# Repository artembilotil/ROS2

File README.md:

# Самостійна робота 1. ROS 2: workspace, ООП-nodes та ESP32 через micro-ROS

**Студент:** Artem Bilotil
**Група:** Рт-2

**Workspace:** `ros2_stud_bilotil_ws`
**Пакет C++:** `stud_bilotil_cpp_pkg`
**Пакет Python:** `stud_bilotil_py_pkg`
**Основний topic (текстові повідомлення):** `/stud_bilotil/message`

---

## Схема системи (поточний стан, Етапи 1–7)

```text
                 ros2_stud_bilotil_ws
                          │
         ┌────────────────┴────────────────┐
         │                                  │
  stud_bilotil_cpp_pkg              stud_bilotil_py_pkg
         │                                  │
 stud_bilotil_publisher      stud_bilotil_subscriber_1/2/3
         │                                  │
         └────────► /stud_bilotil/message ◄─┘
```

---

## 1. Правило іменування

| Об'єкт                        | Ім'я                                   |
|-------------------------------|----------------------------------------|
| Workspace                     | `ros2_stud_bilotil_ws`                 |
| C++ package                   | `stud_bilotil_cpp_pkg`                 |
| Python package                | `stud_bilotil_py_pkg`                  |
| Node — publisher              | `stud_bilotil_publisher`               |
| Node — subscriber             | `stud_bilotil_subscriber`              |
| Node — монітор температури    | `stud_bilotil_temperature_monitor`     |
| Node на мікроконтролері       | `stud_bilotil_esp32`                   |
| Topic — текстові повідомлення | `/stud_bilotil/message`                |
| Topic — температура, °C       | `/stud_bilotil/temperature/celsius`    |
| Topic — температура, °F       | `/stud_bilotil/temperature/fahrenheit` |

---

## 2. Стиль коду

Обидва nodes реалізовано класами:

- `StudentPublisher` успадковує `rclcpp::Node` (C++), усі ROS-сутності (`publisher_`,
  `timer_`, `counter_`) — приватні поля класу, `main()` містить лише
  `rclcpp::init()` → `std::make_shared<StudentPublisher>()` → `rclcpp::spin()` →
  `rclcpp::shutdown()`.
- `StudentSubscriber` успадковує `rclpy.node.Node` (Python), конструктор викликає
  `super().__init__(...)`, `listener_callback` — метод класу.

---

## 3. Етап 1. Власний workspace

### Структура каталогів

| Каталог | Опис |
|---|---|
| `src` | Містить початковий вихідний код (source code) усіх створених або завантажених пакетів ROS 2. |
| `build` | Використовується системою збірки `colcon` для зберігання проміжних файлів компіляції та конфігурації. |
| `install` | Містить готові зібрані виконувані файли, бібліотеки, скрипти та `setup.bash` для їх підключення до середовища. |
| `log` | Зберігає текстові файли журналів (логів) із детальним звітом про процес виконання команд `colcon build`. |

### Вивід перевірки

```text
ros@ros:~/ros2_stud_bilotil_ws$ printenv | grep ROS
ROS_VERSION=2
ROS_PYTHON_VERSION=3
ROS_AUTOMATIC_DISCOVERY_RANGE=SUBNET
ROS_DISTRO=jazzy

ros@ros:~/ros2_stud_bilotil_ws$echo$AMENT_PREFIX_PATH
/home/ros/ros2_stud_bilotil_ws/install/stud_bilotil_py_pkg:/home/ros/ros2_stud_bilotil_ws/install/stud_bilotil_cpp_pkg:/opt/ros/jazzy

### Чому `install/setup.bash` підключається після `/opt/ros/jazzy/setup.bash`, а не замість нього

Файл `install/setup.bash` локального workspace підключається після системного
`/opt/ros/jazzy/setup.bash`, оскільки ROS 2 працює за принципом каскадного накладання
середовищ (underlay / overlay). Системний ROS 2 надає базовий фреймворк, стандартні
бібліотеки та типи повідомлень, а локальний workspace будується поверх нього і
додає власні пакети. Послідовне підключення дописує шляхи локального workspace на
початок змінних оточення (наприклад, `AMENT_PREFIX_PATH`), при цьому зберігаючи
доступ до всіх системних ресурсів ROS 2.

---

## 4. Етап 2. Два packages

Створено два пакети у `~/ros2_stud_bilotil_ws/src/`:

| Package                | Build type    | Залежності          |
|------------------------|---------------|---------------------|
| `stud_bilotil_cpp_pkg` | `ament_cmake` | `rclcpp`, `std_msgs`|
| `stud_bilotil_py_pkg`  | `ament_python`| `rclpy`, `std_msgs` |

### Структура C++ package

```text
stud_bilotil_cpp_pkg/
├── include/
│   └── stud_bilotil_cpp_pkg/
│       └── student_publisher.hpp
├── src/
│   ├── student_publisher.cpp
│   └── main.cpp
├── CMakeLists.txt
└── package.xml
```

### Структура Python package

```text
stud_bilotil_py_pkg/
├── stud_bilotil_py_pkg/
│   ├── __init__.py
│   ├── student_subscriber.py
│   └── temperature_monitor.py
├── resource/
├── setup.py
├── setup.cfg
└── package.xml
```

### Перевірка (наявність обох пакетів)

```text
ros@ros:~/ros2_stud_bilotil_ws$ ros2 pkg list | grep bilotil
stud_bilotil_cpp_pkg
stud_bilotil_py_pkg
ros@ros:~/ros2_stud_bilotil_ws$ 

```

---

## 5. Етап 3. C++ Publisher

**Node:** `stud_bilotil_publisher`

| Параметр                        | Значення                |
|---------------------------------|-------------------------|
| Topic                           | `/stud_bilotil/message` |
| Тип повідомлення                | `std_msgs/msg/String`   |
| Частота | 2 Hz (таймер 500 мс)  |                         |
| Формат повідомлення             | `Bilotil  | Message #N` |

### Код `student_publisher.hpp`

```cpp
#ifndef STUDENT_PUBLISHER_HPP_
#define STUDENT_PUBLISHER_HPP_

#include "rclcpp/rclcpp.hpp"
#include "std_msgs/msg/string.hpp"

class StudentPublisher : public rclcpp::Node {
public:
    StudentPublisher();
private:
    void timer_callback();
    rclcpp::Publisher<std_msgs::msg::String>::SharedPtr publisher_;
    rclcpp::TimerBase::SharedPtr timer_;
    size_t counter_;
};

#endif 
```

### Код `student_publisher.cpp`

```cpp
#include "stud_bilotil_cpp_pkg/student_publisher.hpp"

StudentPublisher::StudentPublisher() : Node("stud_bilotil_publisher"), counter_(0) {
    publisher_ = this->create_publisher<std_msgs::msg::String>("/stud_bilotil/message", 10);
    timer_ = this->create_wall_timer(
        std::chrono::milliseconds(500),
        std::bind(&StudentPublisher::timer_callback, this)
    );
}

void StudentPublisher::timer_callback() {
    auto message = std_msgs::msg::String();
    message.data = "Bilotil | Message #" + std::to_string(counter_);
    RCLCPP_INFO(this->get_logger(), "Publishing: '%s'", message.data.c_str());
    publisher_->publish(message);
    counter_++;
} 
```

### Код `main.cpp`

```cpp
#include "stud_bilotil_cpp_pkg/student_publisher.hpp"

int main(int argc, char * argv[]) {
    rclcpp::init(argc, argv);
    rclcpp::spin(std::make_shared<StudentPublisher>());
    rclcpp::shutdown();
    return 0;
} 
```

### Код `CMakeLists.txt`

```cmake
cmake_minimum_required(VERSION 3.8)
project(stud_bilotil_cpp_pkg)

if(CMAKE_COMPILER_IS_GNUCXX OR CMAKE_CXX_COMPILER_ID MATCHES "Clang")
  add_compile_options(-Wall -Wextra -Wpedantic)
endif()

find_package(ament_cmake REQUIRED)
find_package(rclcpp REQUIRED)
find_package(std_msgs REQUIRED)

include_directories(include)

add_executable(stud_bilotil_publisher
  src/student_publisher.cpp
  src/main.cpp
)

ament_target_dependencies(stud_bilotil_publisher
  rclcpp
  std_msgs
)

install(TARGETS
  stud_bilotil_publisher
  DESTINATION lib/${PROJECT_NAME}
)

ament_package()
```

### Перевірка запуску

```text
$ cd ~/ros2_stud_bilotil_ws
$ colcon build --packages-select stud_bilotil_cpp_pkg
$ source install/setup.bash
$ ros2 run stud_bilotil_cpp_pkg stud_bilotil_publisher
[INFO] [timestamp] [stud_bilotil_publisher]: Publishing: 'Bilotil | Message #0'
[INFO] [timestamp] [stud_bilotil_publisher]: Publishing: 'Bilotil | Message #1'
[INFO] [timestamp] [stud_bilotil_publisher]: Publishing: 'Bilotil | Message #2'
```

---

## 6. Етап 4. Python Subscriber

**Node:** `stud_bilotil_subscriber`, підписаний на `/stud_bilotil/message`.

### Код `student_subscriber.py`

```python
import rclpy
from rclpy.node import Node
from std_msgs.msg import String

class StudentSubscriber(Node):
    def __init__(self):
        super().__init__('stud_bilotil_subscriber')
        self.subscription = self.create_subscription(
            String,
            '/stud_bilotil/message',
            self.listener_callback,
            10
        )
        self.subscription  # Запобігає видаленню змінної збирачем сміття

    def listener_callback(self, msg):
        self.get_logger().info(f'I heard: "{msg.data}"')

def main(args=None):
    rclpy.init(args=args)
    node = StudentSubscriber()
    rclpy.spin(node)
    node.destroy_node()
    rclpy.shutdown()

if __name__ == '__main__':
    main() 
```

### Код `setup.py`

```python
from setuptools import find_packages, setup

package_name = 'stud_bilotil_py_pkg'

setup(
    name=package_name,
    version='0.0.0',
    packages=find_packages(exclude=['test']),
    data_files=[
        ('share/ament_index/resource_index/packages',
            ['resource/' + package_name]),
        ('share/' + package_name, ['package.xml']),
    ],
    install_requires=['setuptools'],
    zip_safe=True,
    maintainer='ros',
    maintainer_email='ros@todo.todo',
    description='Python package for ROS 2 lab',
    license='TODO: License declaration',
    tests_require=['pytest'],
    entry_points={
        'console_scripts': [
            'stud_bilotil_subscriber = stud_bilotil_py_pkg.student_subscriber:main',
            'stud_bilotil_temperature_monitor = stud_bilotil_py_pkg.temperature_monitor:main',
        ],
    },
)
```

### Перевірка (Publisher + Subscriber одночасно, два різні термінали)

**Термінал 1 (Publisher):**
```text
$ source ~/ros2_stud_bilotil_ws/install/setup.bash
$ ros2 run stud_bilotil_cpp_pkg stud_bilotil_publisher
```

**Термінал 2 (Subscriber):**
```text
$ source ~/ros2_stud_bilotil_ws/install/setup.bash
$ ros2 run stud_bilotil_py_pkg stud_bilotil_subscriber
[INFO] [timestamp] [stud_bilotil_subscriber]: I heard: "Bilotil | Message #0"
[INFO] [timestamp] [stud_bilotil_subscriber]: I heard: "Bilotil | Message #1"
[INFO] [timestamp] [stud_bilotil_subscriber]: I heard: "Bilotil | Message #2"
```

---

## 7. Етап 5. Дослідження системи через ROS 2 CLI

Виконано (у Терміналі 3, коли publisher і subscriber вже працювали) сім
діагностичних команд ROS 2 CLI.

**1. Список активних nodes** — `ros2 node list`
```text
/stud_bilotil_publisher
/stud_bilotil_subscriber
```

**2. Список активних topics** — `ros2 topic list -t`
```text
/parameter_events [rcl_interfaces/msg/ParameterEvent]
/rosout [rcl_interfaces/msg/Log]
/stud_bilotil/message [std_msgs/msg/String]
```

**3. Publishers/subscribers конкретного node** — `ros2 node info /stud_bilotil_publisher`
```text
/stud_bilotil_publisher
  Subscribers:
    /parameter_events: rcl_interfaces/msg/ParameterEvent
  Publishers:
    /parameter_events: rcl_interfaces/msg/ParameterEvent
    /rosout: rcl_interfaces/msg/Log
    /stud_bilotil/message: std_msgs/msg/String
  Service Servers:
    /stud_bilotil_publisher/describe_parameters: rcl_interfaces/srv/DescribeParameters
    /stud_bilotil_publisher/get_parameter_types: rcl_interfaces/srv/GetParameterTypes
    /stud_bilotil_publisher/get_parameters: rcl_interfaces/srv/GetParameters
    /stud_bilotil_publisher/get_type_description: type_description_interfaces/srv/GetTypeDescription
    /stud_bilotil_publisher/list_parameters: rcl_interfaces/srv/ListParameters
    /stud_bilotil_publisher/set_parameters: rcl_interfaces/srv/SetParameters
    /stud_bilotil_publisher/set_parameters_atomically: rcl_interfaces/srv/SetParametersAtomically
  Service Clients:

  Action Servers:

  Action Clients:
```

**4. Тип і підключення topic** — `ros2 topic info /stud_bilotil/message`
```text
Type: std_msgs/msg/String
Publisher count: 1
Subscription count: 1
```

**5. Структура типу повідомлення** — `ros2 interface show std_msgs/msg/String`
```text
# This was originally provided as an example message.
# It is deprecated as of Foxy
# It is recommended to create your own semantically meaningful message.
# However if you would like to continue using this please use the equivalent in example_msgs.

string data
```

**6. Читання повідомлень з topic** — `ros2 topic echo /stud_bilotil/message`
```text
ros@ros:~/ros2_stud_bilotil_ws$ ros2 topic echo /stud_bilotil/message
data: 'Bilotil | Message #10653'
---
data: 'Bilotil | Message #10654'
---
data: 'Bilotil | Message #10655'
---

```
*(зупинено вручну через Ctrl+C)*

**7. Фактична частота публікації** — `ros2 topic hz /stud_bilotil/message`
```text
average rate: 1.992
	min: 0.499s max: 0.509s std dev: 0.00418s window: 4
average rate: 2.001
	min: 0.492s max: 0.509s std dev: 0.00560s window: 9
average rate: 2.000
	min: 0.492s max: 0.509s std dev: 0.00492s window: 12
average rate: 2.000
	min: 0.479s max: 0.522s std dev: 0.00828s window: 32
```
*(зупинено вручну через Ctrl+C)*

**Висновок:** фактична середня частота публікації (~2.000 Hz) точно відповідає
заданій у коді C++ частоті таймера (період 500 мс = 2 Hz). Значення `min`/`max`
коливаються в межах кількох мілісекунд, що є нормальним джерелом джитера в
непристосованому до real-time середовищі ОС.

---

## 8. Етап 6. Експеримент з трьома Subscribers

Запущено три екземпляри одного й того самого Python-вузла без зміни його сирцевого коду, використовуючи ремапінг імені вузла (`--ros-args -r __node:=...`).

### Одночасна робота 4 терміналів:

### Детальна інформація про топік з 3 підписниками (`ros2 topic info /stud_bilotil/message --verbose`):
```text
Type: std_msgs/msg/String

Publisher count: 1

Node name: stud_bilotil_publisher
Node namespace: /
Topic type: std_msgs/msg/String
Topic type hash: RIHS01_df668c740482bbd48fb39d76a70dfd4bd59db1288021743503259e948f6b1a18
Endpoint type: PUBLISHER
GID: 01.0f.65.91.22.0c.93.1b.00.00.00.00.00.00.14.03
QoS profile:
  Reliability: RELIABLE
  History (Depth): UNKNOWN
  Durability: VOLATILE
  Lifespan: Infinite
  Deadline: Infinite
  Liveliness: AUTOMATIC
  Liveliness lease duration: Infinite

Subscription count: 3

Node name: stud_bilotil_subscriber_1
Node namespace: /
Topic type: std_msgs/msg/String
Topic type hash: RIHS01_df668c740482bbd48fb39d76a70dfd4bd59db1288021743503259e948f6b1a18
Endpoint type: SUBSCRIPTION
GID: 01.0f.65.91.99.0c.ad.33.00.00.00.00.00.00.13.04
QoS profile:
  Reliability: RELIABLE
  History (Depth): UNKNOWN
  Durability: VOLATILE
  Lifespan: Infinite
  Deadline: Infinite
  Liveliness: AUTOMATIC
  Liveliness lease duration: Infinite

Node name: stud_bilotil_subscriber_2
Node namespace: /
Topic type: std_msgs/msg/String
Topic type hash: RIHS01_df668c740482bbd48fb39d76a70dfd4bd59db1288021743503259e948f6b1a18
Endpoint type: SUBSCRIPTION
GID: 01.0f.65.91.b4.0c.9e.f5.00.00.00.00.00.00.13.04
QoS profile:
  Reliability: RELIABLE
  History (Depth): UNKNOWN
  Durability: VOLATILE
  Lifespan: Infinite
  Deadline: Infinite
  Liveliness: AUTOMATIC
  Liveliness lease duration: Infinite

Node name: stud_bilotil_subscriber_3
Node namespace: /
Topic type: std_msgs/msg/String
Topic type hash: RIHS01_df668c740482bbd48fb39d76a70dfd4bd59db1288021743503259e948f6b1a18
Endpoint type: SUBSCRIPTION
GID: 01.0f.65.91.cf.0c.06.8b.00.00.00.00.00.00.13.04
QoS profile:
  Reliability: RELIABLE
  History (Depth): UNKNOWN
  Durability: VOLATILE
  Lifespan: Infinite
  Deadline: Infinite
  Liveliness: AUTOMATIC
  Liveliness lease duration: Infinite
```

### Відповіді на контрольні запитання Етапу 6:

1. **Чому одне повідомлення доходить до всіх трьох nodes і скільки разів воно публікується?**  
   Повідомлення публікується паблішером у мережний шар (DDS) **лише один раз**. Middleware ROS 2 (DDS) самостійно дублює і розсилає цей мережевий пакет усім 3 підписаним вузлам (архітектура 1-до-N).

2. **У якій ситуації довелося б використати Service замість Topic?**  
   Service (модель запит-відповідь) потрібен у ситуаціях, коли необхідна точкова адресація «один-до-одного» із підтвердженням виконання (наприклад, викликати функцію скидання лічильника, запитати конкретну конфігурацію або відправити команду на виконання конкретної дії).

  ## 9. Етап 7. rqt та rqt_graph

Графічна утиліта `rqt_graph` використовується для візуалізації обчислювального графа (Computational Graph) ROS 2 у реальному часі.

### Загальний вигляд графа (усі 4 вузли активні):

---

### Результати експерименту та аналіз змін у графі

#### Крок 1. Зупинка вузла `stud_bilotil_subscriber_3`
* **Що саме зникло:** Зник овал вузла `/stud_bilotil_subscriber_3` та одна з трьох вихідних стрілок, що вела до нього від топіка.
* **Що залишилося:** Овал паблішера `/stud_bilotil_publisher`, топік `/stud_bilotil/message` та вузли `subscriber_1` i `subscriber_2`.
* **Скріншот:**

#### Крок 3. Зупинка вузла `stud_bilotil_publisher`
* **Що саме зникло:** Зник овал вузла `/stud_bilotil_publisher` та вхідна стрілка, яка вела від нього до топіка.
* **Що залишилося:** Сам топік `/stud_bilotil/message` та три підписані вузли `subscriber_1`, `subscriber_2`, `subscriber_3` зі стрілками до них.
* **Скріншот:**

---

### Чому в цих двох випадках результат такий і чому топік не зникає?

1. **При зупинці `subscriber_3`:** Зникає лише конкретна нода-підписник і зв'язок із нею. Топік залишається, оскільки паблішер продовжує в нього мовити, а інші два підписники продовжують з нього читати.
2. **При зупинці `publisher`:** Зникає нода-видавець і вхідна стрілка публікації. Проте сам прямокутник топіка `/stud_bilotil/message` **не зникає з графа**, тому що у ROS 2 підписники все ще залишаються зареєстрованими в графі (у DDS-метаданих) і очікують на дані.

**Висновок про відмінність:** 
В обох випадках зникає відповідна нода (node) та її стрілка (зв'язок). Проте топік (topic) зберігається в обох сценаріях, оскільки в системі залишається принаймні один активний endpoint (або publisher, або хоча б один subscriber).

# 10. Етап 8. STM32 i температурний датчик DHT22

## Інформація про датчик

| Пункт | Що вказати / Значення |
| :--- | :--- |
| **Модель** | DHT22 (AM2302) |
| **Живлення** | Напруга: 3.3V – 5.5V DC; Струм споживання: 1.0–1.5 мА (активний), 40–50 мкА (очікування) |
| **Інтерфейс** | Single-Wire (цифровий однопровідний протокол з часовими інтервалами) |
| **Діапазон** | Температура: від -40 °C до +80 °C (Вологість: 0–100% RH) |
| **Точність** | Температура: ±0.5 °C (Вологість: ±2% RH) |
| **Роздільна здатність** | 0.1 °C (0.1% RH) |
| **Підключення** | **VCC** $\rightarrow$ `3.3V`<br>**DATA** $\rightarrow$ `PA1` (або довільний GPIO, ініціалізований як `DHT_22_Pin`) з зовнішнім/внутрішнім підтягуючим резистором 4.7–10 кОм до `3.3V`<br>**NC** $\rightarrow$ Не використовується<br>**GND** $\rightarrow$ `GND` |

---

## Програмна реалізація (STM32 HAL + USB CDC)

Для мікросекундних затримок використовується апаратний таймер `TIM1` (`Prescaler = 95`, 1 тік = 1 мкс). Вивід даних здійснюється через **USB Virtual COM Port (CDC)**.

### Основний фрагмент коду зчитування (`main.c`)

```c
#include "main.h"
#include "usb_device.h"
#include "usbd_cdc_if.h"
#include <stdio.h>
#include <string.h>

extern TIM_HandleTypeDef htim1;
char usb_buf[128];

// Мікросекундна затримка через TIM1
void delay_us(uint16_t us) {
    __HAL_TIM_SET_COUNTER(&htim1, 0);
    while (__HAL_TIM_GET_COUNTER(&htim1) < us);
}

// Запит до датчика DHT22
uint8_t DHT22_Start(void) {
    uint8_t Response = 0;
    Set_Pin_Output(DHT_22_GPIO_Port, DHT_22_Pin);

    HAL_GPIO_WritePin(DHT_22_GPIO_Port, DHT_22_Pin, GPIO_PIN_RESET);
    delay_us(1200); // Стартовий імпульс 1.2 мс

    HAL_GPIO_WritePin(DHT_22_GPIO_Port, DHT_22_Pin, GPIO_PIN_SET);
    delay_us(30);

    Set_Pin_Input(DHT_22_GPIO_Port, DHT_22_Pin);

    delay_us(40);
    if (!(HAL_GPIO_ReadPin(DHT_22_GPIO_Port, DHT_22_Pin))) {
        delay_us(80);
        if ((HAL_GPIO_ReadPin(DHT_22_GPIO_Port, DHT_22_Pin))) Response = 1;
        else Response = 0;
    }
    while ((HAL_GPIO_ReadPin(DHT_22_GPIO_Port, DHT_22_Pin)));

    return Response;
}

// Зчитування байта
uint8_t DHT22_Read_Byte(void) {
    uint8_t i = 0, j;
    for (j = 0; j < 8; j++) {
        while (!(HAL_GPIO_ReadPin(DHT_22_GPIO_Port, DHT_22_Pin)));
        delay_us(40);
        if (!(HAL_GPIO_ReadPin(DHT_22_GPIO_Port, DHT_22_Pin))) {
            i &= ~(1 << (7 - j));
        } else {
            i |= (1 << (7 - j));
            while ((HAL_GPIO_ReadPin(DHT_22_GPIO_Port, DHT_22_Pin)));
        }
    }
    return i;
}

// Головний цикл
while (1) {
    if (DHT22_Start()) {
        Rh_byte1 = DHT22_Read_Byte();
        Rh_byte2 = DHT22_Read_Byte();
        Temp_byte1 = DHT22_Read_Byte();
        Temp_byte2 = DHT22_Read_Byte();
        SUM = DHT22_Read_Byte();

        if (SUM == ((Rh_byte1 + Rh_byte2 + Temp_byte1 + Temp_byte2) & 0xFF)) {
            RAW_Humidity = (Rh_byte1 << 8) | Rh_byte2;
            RAW_Temp = (Temp_byte1 << 8) | Temp_byte2;

            int temp_int = RAW_Temp / 10;
            int temp_dec = RAW_Temp % 10;
            int hum_int = RAW_Humidity / 10;
            int hum_dec = RAW_Humidity % 10;

            snprintf(usb_buf, sizeof(usb_buf), "Temp: %d.%d C, Humidity: %d.%d %%\r\n", 
                     temp_int, temp_dec, hum_int, hum_dec);
            CDC_Transmit_FS((uint8_t*)usb_buf, strlen(usb_buf));
        }
    }
    HAL_Delay(2000);
}
```

Результати роботи
Вивід серійного монітору

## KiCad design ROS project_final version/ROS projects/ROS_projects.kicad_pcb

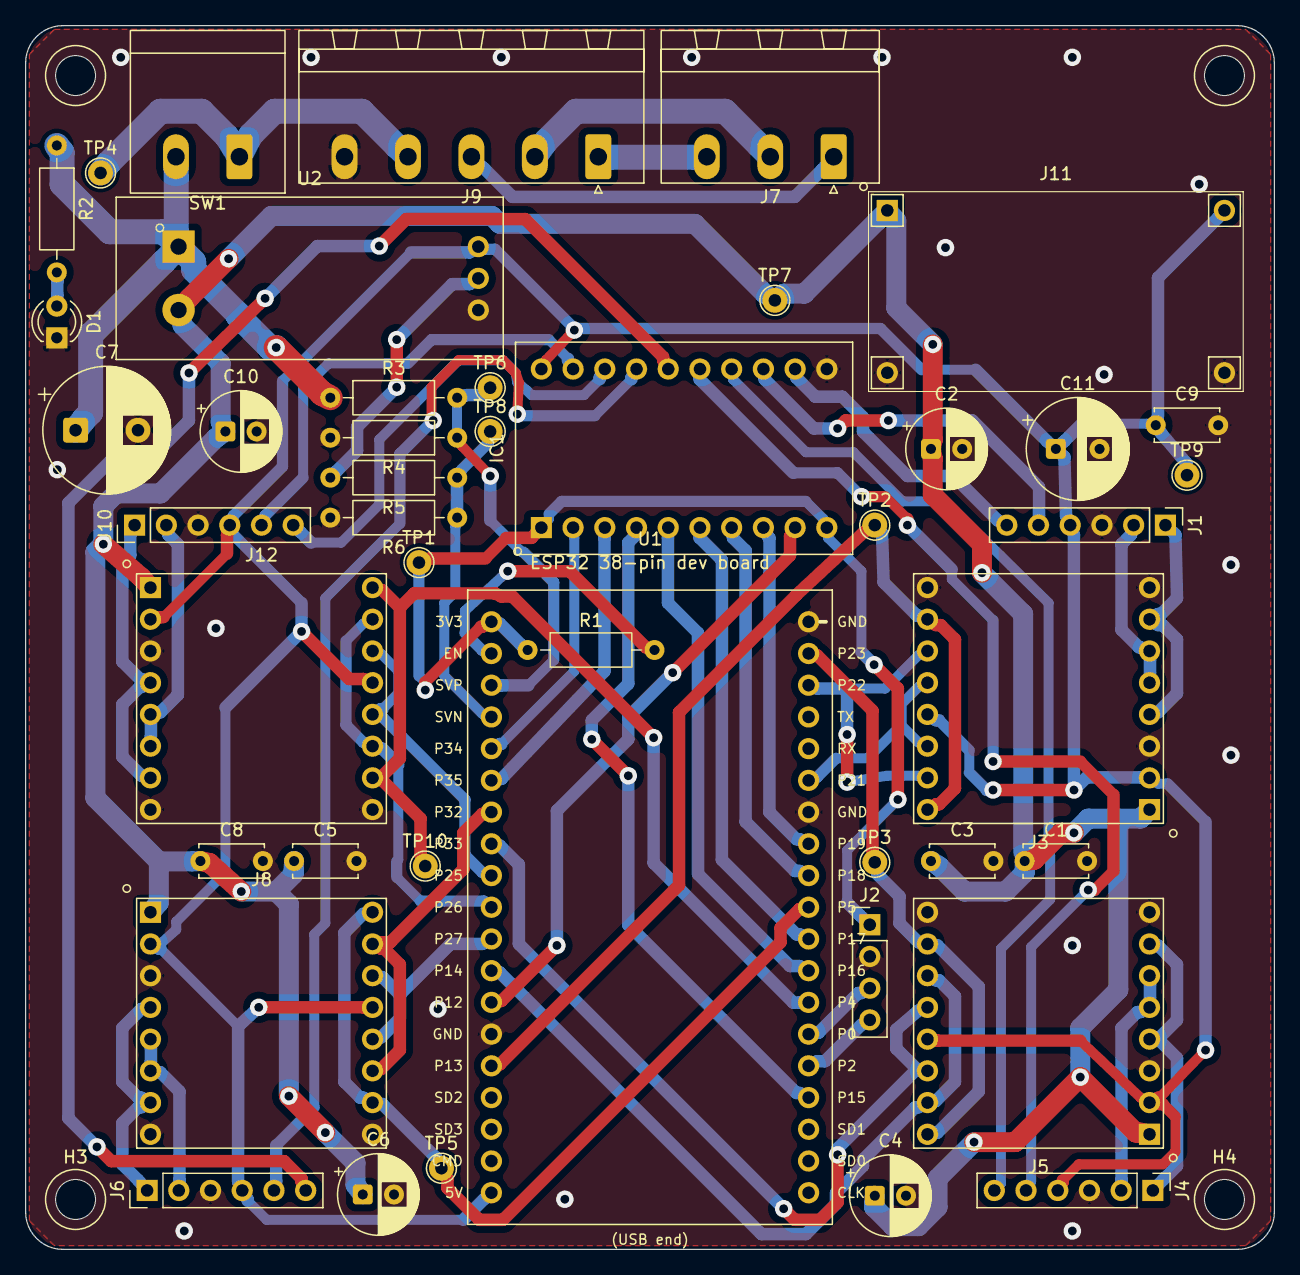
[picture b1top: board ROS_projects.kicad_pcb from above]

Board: 2 copper layers, 100.0 x 98.0 mm, 48 parts (0 on the bottom side), 52 nets.

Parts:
C1, C3, C5, C8, C9: 100nF; C_Disc_D5.0mm_W2.5mm_P5.00mm
C2, C4, C6, C10: 220uF; CP_Radial_D6.3mm_P2.50mm
C7: 2200uF; CP_Radial_D10.0mm_P5.00mm
C11: 470uF; CP_Radial_D8.0mm_P3.50mm
D1: LED_Small; LED_D3.0mm
H1, H2, H3, H4: MountingHole; MountingHole_3.2mm
IC1: TXS0108E; HW-221_TXS0108E_Module_27x17
J1, J4, J6, J10: Motor_FIT0450; PinHeader_1x06_P2.54mm_Vertical
J2: Conn_01x04; PinHeader_1x04_P2.54mm_Vertical
J3, J5, J8, J12: TB6612FNG; HW-166_TB6612FNG_Module_20x20
J7: BATTERY_2S_7.4V; PhoenixContact_MSTBA_2,5_3-G-5,08_1x03_P5.08mm_Horizontal
J9: BMS 2S 20A; PhoenixContact_MSTBA_2,5_5-G-5,08_1x05_P5.08mm_Horizontal
J11: Module_XL63070-5V; XL63070_TPS63070_Module_Socket_4corners_30x16
R1, R4, R5: 10K; R_Axial_DIN0207_L6.3mm_D2.5mm_P10.16mm_Horizontal
R2: 1K; R_Axial_DIN0207_L6.3mm_D2.5mm_P10.16mm_Horizontal
R3, R6: 20K; R_Axial_DIN0207_L6.3mm_D2.5mm_P10.16mm_Horizontal
SW1: SW_SPST; PhoenixContact_MSTBA_2,5_2-G-5,08_1x02_P5.08mm_Horizontal
TP1: 3.3 V; TestPoint_THTPad_D2.0mm_Drill1.0mm
TP2: M4_PWM; TestPoint_THTPad_D2.0mm_Drill1.0mm
TP3: M3_PWM; TestPoint_THTPad_D2.0mm_Drill1.0mm
TP4: Battery; TestPoint_THTPad_D2.0mm_Drill1.0mm
TP5: M2_PWM; TestPoint_THTPad_D2.0mm_Drill1.0mm
TP6: VBAT_SENSE; TestPoint_THTPad_D2.0mm_Drill1.0mm
TP7: 7.4 V; TestPoint_THTPad_D2.0mm_Drill1.0mm
TP8: CURRENT_SENSE; TestPoint_THTPad_D2.0mm_Drill1.0mm
TP9: 5 V; TestPoint_THTPad_D2.0mm_Drill1.0mm
TP10: M1_PWM; TestPoint_THTPad_D2.0mm_Drill1.0mm
U1: ESP32-WROOM-32; Socket_ESP32_DevBoard_38_2x19_P2.54mm_Row25.4mm
U2: ACS712xLCTR-30A; ACS712_CurrentSensor_Module_31x13

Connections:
+3V3: IC1.2 (VCCA), IC1.10 (OE), J2.1, R1.1, TP1.1 (1_1), U1.32 (NC)
+5V: C9.1, C11.1, IC1.19 (VCCB), J1.4, J3.2 (VCC), J3.12 (STBY), J4.4, J5.2 (VCC), J5.12 (STBY), J6.4, J8.2 (VCC), J8.12 (STBY), J10.4, J11.3 (VOUT), J12.2 (VCC), J12.12 (STBY), TP9.1 (1_1), U1.2 (VDD), U2.8 (VCC)
+7.4V: C1.1, C2.1, C3.1, C4.1, C5.1, C6.1, C8.1, C10.1, J3.1 (VM), J5.1 (VM), J8.1 (VM), J11.1 (VIN), J12.1 (VM), TP7.1 (1_1), U2.3 (IP-)
/CURRENT_SENSE: R5.1, R6.1, TP8.1 (1_1), U1.5 (SENSOR_VN)
/E1_A_3V3: IC1.1 (A1), U1.6 (IO34)
/E1_A_5V: IC1.20 (B1), J10.5
/E1_B_3V3: IC1.3 (A2), U1.7 (IO35)
/E1_B_5V: IC1.18 (B2), J10.6
/E2_A_3V3: IC1.4 (A3), U1.23 (IO15)
/E2_A_5V: IC1.17 (B3), J6.5
/E2_B_3V3: IC1.5 (A4), U1.27 (IO16)
/E2_B_5V: IC1.16 (B4), J6.6
/E3_A_3V3: IC1.6 (A5), U1.28 (IO17)
/E3_A_5V: IC1.15 (B5), J4.5
/E3_B_3V3: IC1.7 (A6), U1.30 (IO18)
/E3_B_5V: IC1.14 (B6), J4.6
/E4_A_3V3: IC1.8 (A7), U1.31 (IO19)
/E4_A_5V: IC1.13 (B7), J1.5
/E4_B_3V3: IC1.9 (A8), U1.14 (IO12)
/E4_B_5V: IC1.12 (B8), J1.6
/M1_IN1: J12.11 (AIN1), J12.13 (BIN1), U1.10 (IO25)
/M1_IN2: J12.10 (AIN2), J12.14 (BIN2), U1.11 (IO26)
/M1_PWM: J12.9 (PWMA), J12.15 (PWMB), TP10.1 (1_1), U1.26 (IO4)
/M2_IN1: J8.11 (AIN1), J8.13 (BIN1), U1.12 (IO27)
/M2_IN2: J8.10 (AIN2), J8.14 (BIN2), U1.8 (IO32)
/M2_PWM: J8.9 (PWMA), J8.15 (PWMB), TP5.1 (1_1), U1.29 (IO5)
/M3_IN1: J5.11 (AIN1), J5.13 (BIN1), U1.9 (IO33)
/M3_IN2: J5.10 (AIN2), J5.14 (BIN2), U1.13 (IO14)
/M3_PWM: J5.9 (PWMA), J5.15 (PWMB), TP3.1 (1_1), U1.37 (IO23)
/M4_IN1: J3.11 (AIN1), J3.13 (BIN1), U1.33 (IO21)
/M4_IN2: J3.10 (AIN2), J3.14 (BIN2), U1.36 (IO22)
/M4_PWM: J3.9 (PWMA), J3.15 (PWMB), TP2.1 (1_1), U1.16 (IO13)
/SP_1: J2.3, U1.25 (IO0)
/SP_2: J2.4, U1.24 (IO2)
/VBAT_SENSE: R3.2, R4.1, TP6.1 (1_1), U1.4 (SENSOR_VP)
GND: C1.2, C2.2, C3.2, C4.2, C5.2, C6.2, C7.2, C8.2, C9.2, C10.2, C11.2, D1.1 (K), IC1.11 (GND), J1.3, J2.2, J3.3 (GND), J3.8 (GND), J3.16 (GND), J4.3, J5.3 (GND), J5.8 (GND), J5.16 (GND), J6.3, J8.3 (GND), J8.8 (GND), J8.16 (GND), J9.5, J10.3, J11.2 (GND), J11.4 (GND), J12.3 (GND), J12.8 (GND), J12.16 (GND), R4.2, R6.2, U1.1 (GND), U1.15 (GND), U1.38 (GND), U2.5 (GND)
unnamed: D1.2 (A), R2.2
unnamed: J1.1, J3.4 (A1), J3.6 (B1)
unnamed: J1.2, J3.5 (A2), J3.7 (B2)
unnamed: J4.1, J5.4 (A1), J5.6 (B1)
unnamed: J4.2, J5.5 (A2), J5.7 (B2)
unnamed: J6.1, J8.4 (A1), J8.6 (B1)
unnamed: J6.2, J8.5 (A2), J8.7 (B2)
unnamed: J7.1, J9.3
unnamed: J7.2, J9.2
unnamed: J7.3, J9.1
unnamed: J9.4, SW1.1 (A), TP4.1 (1_1)
unnamed: J10.1, J12.4 (A1), J12.6 (B1)
unnamed: J10.2, J12.5 (A2), J12.7 (B2)
unnamed: C7.1, R2.1, R3.1, SW1.2 (B), U2.1 (IP+)
unnamed: R1.2, U1.3 (EN)
unnamed: R5.2, U2.7 (VIOUT)
